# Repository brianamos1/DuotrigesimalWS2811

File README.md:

# DuotrigesimalWS2811
A board for driving 32 strings of pixels from a Teensy 4.1. Similar to the OctoWS2811, but with 32 outputs. 

This board interfaces with a Teensy 4.1, and is designed to use the OctoWS2811 library to drive up to 32 strings of LEDS. 

Version 0.2 is designed to use the Amphenol RJHSE508004-ND, which is a four port RJ45 jack.  Version 0.2a uses the Adam Tech MTJG-4-88GX1-FSB, which is a less expensive and more readily available alternative.

The 2x3 pin that connects the board to the Teensy 4.1's ethernet pins is available on digikey and mouser, however is easier to source from PJRC when purchasing the Teensy 4.1.  If you want the teensy to be removable, PJRC is the recommended source for that connector.  If you're going to solder the T4.1 to this board, then it doesn't matter the source for the pins.  ‎

Boards are available for purchase at https://www.tindie.com/products/25767/

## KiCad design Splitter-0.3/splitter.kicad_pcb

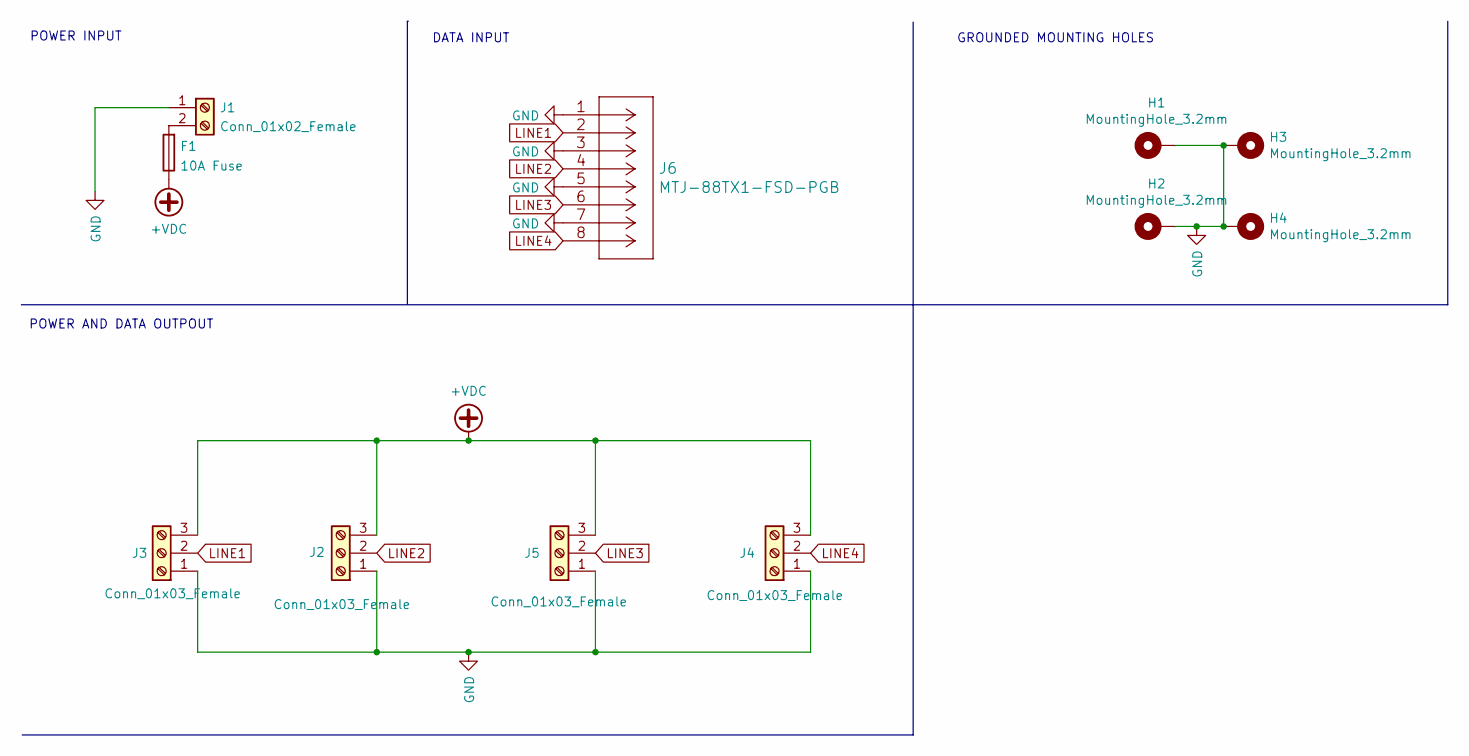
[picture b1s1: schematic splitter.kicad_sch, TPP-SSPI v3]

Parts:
F1: 10A Fuse; Fuseholder_Blade_Mini_Keystone_3568
H1, H2, H3, H4: MountingHole_3.2mm; MountingHole_3.2mm_M3_Pad_Via
J1: Conn_01x02_Female; TerminalBlock_OST_02A150-2_P2.54mm
J2, J3, J4, J5: Conn_01x03_Female; TerminalBlock_OST_03A150-3_P2.54mm
J6: MTJ-88TX1-FSD-PGB; RJ45_AdamTech_MTJ-88TX1-FSD-PGB

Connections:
+VDC: F1.1, J2.3, J3.3, J4.3, J5.3
GND: H1.1, H2.1, H3.1, H4.1, J1.1, J2.1, J3.1, J4.1, J5.1, J6.1, J6.3, J6.5, J6.7, J6.12, J6.13
LINE1: J3.2, J6.2
LINE2: J2.2, J6.4
LINE3: J5.2, J6.6
LINE4: J4.2, J6.8
unnamed: F1.2, J1.2

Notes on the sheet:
DATA INPUT
POWER INPUT
GROUNDED MOUNTING HOLES
POWER AND DATA OUTPOUT

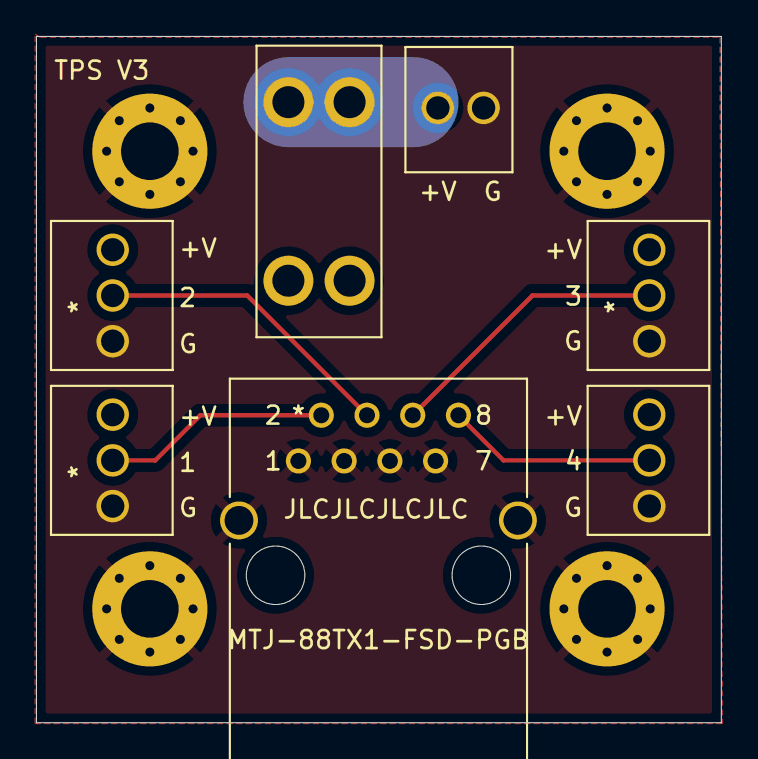
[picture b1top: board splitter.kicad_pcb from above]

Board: 2 copper layers, 38.0 x 38.1 mm, 11 parts (0 on the bottom side), 7 nets.

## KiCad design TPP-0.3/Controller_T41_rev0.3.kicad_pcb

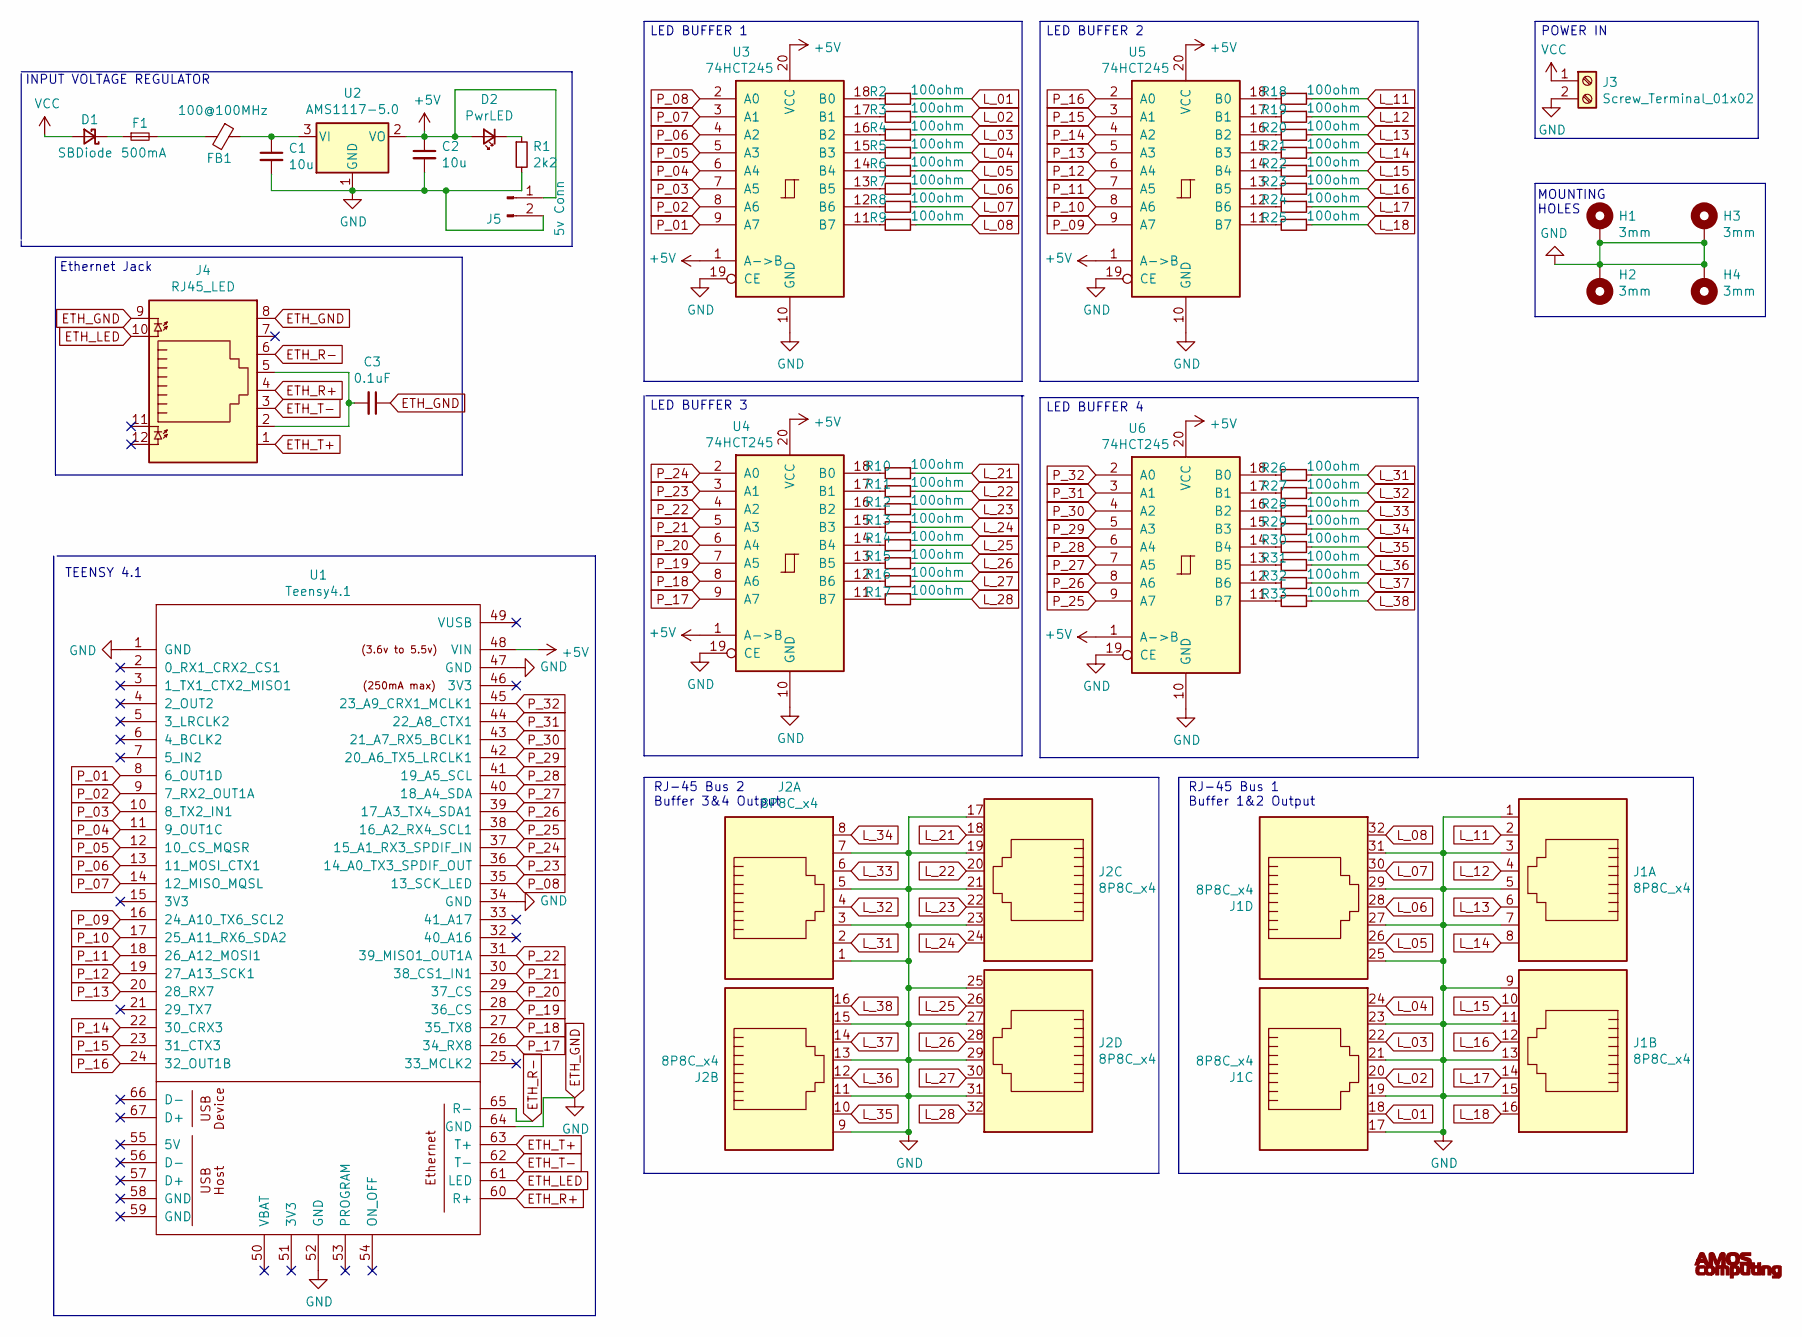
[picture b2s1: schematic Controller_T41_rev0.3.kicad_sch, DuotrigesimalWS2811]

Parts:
C1, C2: 10u; C_1206_3216Metric; LCSC C13585
C3: 0.1uF; C_0805_2012Metric; LCSC C49678
D1: SBDiode; D_SOD-123; Part Number B5819W; LCSC C8598
D2: PwrLED; LED_0603_1608Metric; LCSC C2286
F1: 500mA; Fuse_1206_3216Metric_Pad1.42x1.75mm_HandSolder
FB1: 100@100MHz; L_0805_2012Metric; Part Number GZ2012D101TF Ferrite Bead; LCSC C1015
H1, H2, H3, H4: 3mm; MountingHole_3.2mm_M3_Pad_Via
J1, J2: 8P8C_x4; RJ45_Amphenol_RJHSE508004-ND‎
J3: Screw_Terminal_01x02; TerminalBlock_Phoenix_MKDS-3-2-5.08_1x02_P5.08mm_Horizontal
J4: RJ45_LED; RJ45_Cetus_J1B1211CCD_Horizontal
J5: 5v Conn; PinHeader_1x02_P2.54mm_Vertical
R1: 2k2; R_0805_2012Metric; LCSC C17520
R2, R3, R4, R5, R6, R7, R8, R9, R10, R11, R12, R13, R14, R15, R16, R17, R18, R19, R20, R21, R22, R23, R24, R25, R26, R27, R28, R29, R30, R31, R32, R33: 100ohm; R_01005_0402Metric; LCSC C25076
U1: Teensy4.1; Teensy41
U2: AMS1117-5.0; SOT-223-3_TabPin2; LCSC C6187
U3, U4, U5, U6: 74HCT245; SOIC-20W_7.5x12.8mm_P1.27mm; LCSC C110789

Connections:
+5V: C2.1, D2.2 (A), J5.1, U1.48 (VIN), U2.2 (VO), U3.1 (A->B), U3.20 (VCC), U4.1 (A->B), U4.20 (VCC), U5.1 (A->B), U5.20 (VCC), U6.1 (A->B), U6.20 (VCC)
ETH_GND: C1.2, C2.2, C3.1, H1.1, H2.1, H3.1, H4.1, J1.1, J1.3, J1.5, J1.7, J1.9, J1.11, J1.13, J1.15, J1.17, J1.19, J1.21, J1.23, J1.25, J1.27, J1.29, J1.31, J2.1, J2.3, J2.5, J2.7, J2.9, J2.11, J2.13, J2.15, J2.17, J2.19, J2.21, J2.23, J2.25, J2.27, J2.29, J2.31, J3.2, J4.8, J4.9, J5.2, R1.2, U1.1 (GND), U1.34 (GND), U1.47 (GND), U1.52 (GND), U1.64 (GND), U2.1 (GND), U3.10 (GND), U3.19 (CE), U4.10 (GND), U4.19 (CE), U5.10 (GND), U5.19 (CE), U6.10 (GND), U6.19 (CE)
ETH_LED: J4.10, U1.61 (LED)
ETH_R+: J4.4, U1.60 (R+)
ETH_R-: J4.6, U1.65 (R-)
ETH_T+: J4.1, U1.63 (T+)
ETH_T-: J4.3, U1.62 (T-)
L_01: J1.18, R2.1
L_02: J1.20, R3.1
L_03: J1.22, R4.1
L_04: J1.24, R5.1
L_05: J1.26, R6.1
L_06: J1.28, R7.1
L_07: J1.30, R8.1
L_08: J1.32, R9.1
L_11: J1.2, R18.1
L_12: J1.4, R19.1
L_13: J1.6, R20.1
L_14: J1.8, R21.1
L_15: J1.10, R22.1
L_16: J1.12, R23.1
L_17: J1.14, R24.1
L_18: J1.16, R25.1
L_21: J2.18, R10.1
L_22: J2.20, R11.1
L_23: J2.22, R12.1
L_24: J2.24, R13.1
L_25: J2.26, R14.1
L_26: J2.28, R15.1
L_27: J2.30, R16.1
L_28: J2.32, R17.1
L_31: J2.2, R26.1
L_32: J2.4, R27.1
L_33: J2.6, R28.1
L_34: J2.8, R29.1
L_35: J2.10, R30.1
L_36: J2.12, R31.1
L_37: J2.14, R32.1
L_38: J2.16, R33.1
unnamed: C1.1, FB1.1, U2.3 (VI)
unnamed: C3.2, J4.2, J4.5
unnamed: D1.1 (K), F1.1
unnamed: D2.1 (K), R1.1
unnamed: F1.2, FB1.2
unnamed: R2.2, U3.18 (B0)
unnamed: R3.2, U3.17 (B1)
unnamed: R4.2, U3.16 (B2)
unnamed: R5.2, U3.15 (B3)
unnamed: R6.2, U3.14 (B4)
unnamed: R7.2, U3.13 (B5)
unnamed: R8.2, U3.12 (B6)
unnamed: R9.2, U3.11 (B7)
unnamed: R10.2, U4.18 (B0)
unnamed: R11.2, U4.17 (B1)
unnamed: R12.2, U4.16 (B2)
unnamed: R13.2, U4.15 (B3)
unnamed: R14.2, U4.14 (B4)
unnamed: R15.2, U4.13 (B5)
unnamed: R16.2, U4.12 (B6)
unnamed: R17.2, U4.11 (B7)
unnamed: R18.2, U5.18 (B0)
unnamed: R19.2, U5.17 (B1)
unnamed: R20.2, U5.16 (B2)
unnamed: R21.2, U5.15 (B3)
unnamed: R22.2, U5.14 (B4)
unnamed: R23.2, U5.13 (B5)
unnamed: R24.2, U5.12 (B6)
unnamed: R25.2, U5.11 (B7)
unnamed: R26.2, U6.18 (B0)
unnamed: R27.2, U6.17 (B1)
unnamed: R28.2, U6.16 (B2)
unnamed: R29.2, U6.15 (B3)
unnamed: R30.2, U6.14 (B4)
unnamed: R31.2, U6.13 (B5)
unnamed: R32.2, U6.12 (B6)
unnamed: R33.2, U6.11 (B7)
P_01: U1.8 (6_OUT1D), U3.9 (A7)
P_02: U1.9 (7_RX2_OUT1A), U3.8 (A6)
P_03: U1.10 (8_TX2_IN1), U3.7 (A5)
P_04: U1.11 (9_OUT1C), U3.6 (A4)
P_05: U1.12 (10_CS_MQSR), U3.5 (A3)
P_06: U1.13 (11_MOSI_CTX1), U3.4 (A2)
P_07: U1.14 (12_MISO_MQSL), U3.3 (A1)
P_08: U1.35 (13_SCK_LED), U3.2 (A0)
P_09: U1.16 (24_A10_TX6_SCL2), U5.9 (A7)
P_10: U1.17 (25_A11_RX6_SDA2), U5.8 (A6)
P_11: U1.18 (26_A12_MOSI1), U5.7 (A5)
P_12: U1.19 (27_A13_SCK1), U5.6 (A4)
P_13: U1.20 (28_RX7), U5.5 (A3)
P_14: U1.22 (30_CRX3), U5.4 (A2)
P_15: U1.23 (31_CTX3), U5.3 (A1)
P_16: U1.24 (32_OUT1B), U5.2 (A0)
P_17: U1.26 (34_RX8), U4.9 (A7)
P_18: U1.27 (35_TX8), U4.8 (A6)
P_19: U1.28 (36_CS), U4.7 (A5)
P_20: U1.29 (37_CS), U4.6 (A4)
P_21: U1.30 (38_CS1_IN1), U4.5 (A3)
P_22: U1.31 (39_MISO1_OUT1A), U4.4 (A2)
P_23: U1.36 (14_A0_TX3_SPDIF_OUT), U4.3 (A1)
P_24: U1.37 (15_A1_RX3_SPDIF_IN), U4.2 (A0)
P_25: U1.38 (16_A2_RX4_SCL1), U6.9 (A7)
P_26: U1.39 (17_A3_TX4_SDA1), U6.8 (A6)
P_27: U1.40 (18_A4_SDA), U6.7 (A5)
P_28: U1.41 (19_A5_SCL), U6.6 (A4)
P_29: U1.42 (20_A6_TX5_LRCLK1), U6.5 (A3)
P_30: U1.43 (21_A7_RX5_BCLK1), U6.4 (A2)
P_31: U1.44 (22_A8_CTX1), U6.3 (A1)
P_32: U1.45 (23_A9_CRX1_MCLK1), U6.2 (A0)
VCC: D1.2 (A), J3.1

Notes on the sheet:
INPUT VOLTAGE REGULATOR
MOUNTING HOLES
LED BUFFER 1
RJ-45 Bus 2 Buffer 3&4 Output
Ethernet Jack
LED BUFFER 4
POWER IN
LED BUFFER 2
RJ-45 Bus 1 Buffer 1&2 Output
LED BUFFER 3
TEENSY 4.1

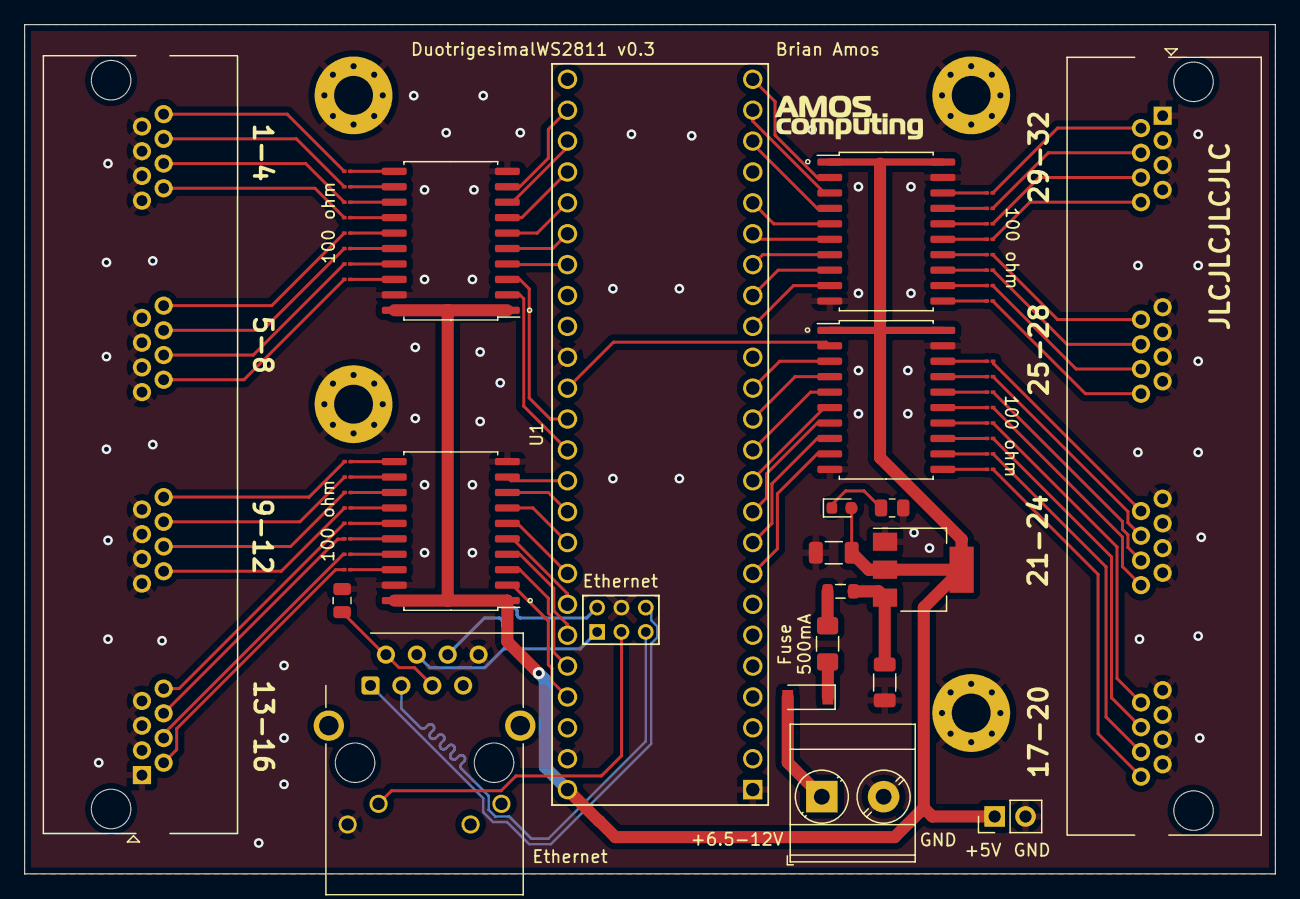
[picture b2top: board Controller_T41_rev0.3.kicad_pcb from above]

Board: 2 copper layers, 102.9 x 69.9 mm, 55 parts (0 on the bottom side), 109 nets.

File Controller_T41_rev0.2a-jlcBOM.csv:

Comment,Designator,Footprint,LCSC
"10u","C1,C2","Capacitor_SMD:C_1206_3216Metric","C13585"
"0.1uF","C3","Capacitor_SMD:C_0805_2012Metric","C49678"
"B5819W","D1","Diode_SMD:D_SOD-123","C8598"
"red","D2","LED_SMD:LED_0603_1608Metric","C2286"
"500mA","F1","Fuse:Fuse_0603_1608Metric_Pad1.05x0.95mm_HandSolder",""
"100@100MHz GZ2012D101TF","FB1","Inductor_SMD:L_0805_2012Metric"," C1015"
"3mm","H1,H2,H3,H4","MountingHole:MountingHole_3.2mm_M3_Pad_Via",""
"8P8C_x4","J1,J2","Controller_T41_rev0.2:MTJG-4-88GX1-FSB",""
"Screw_Terminal_01x02","J3","TerminalBlock_Phoenix:TerminalBlock_Phoenix_MKDS-3-2-5.08_1x02_P5.08mm_Horizontal",""
"RJ45_LED","J4","Connector_RJ:RJ45_Cetus_J1B1211CCD_Horizontal",""
"2k2","R1","Resistor_SMD:R_0805_2012Metric","C17520"
"100ohm","R2,R3,R4,R5,R6,R7,R8,R9,R10,R11,R12,R13,R14,R15,R16,R17,R18,R19,R20,R21,R22,R23,R24,R25,R26,R27,R28,R29,R30,R31,R32,R33","Resistor_SMD:R_1206_3216Metric","C17901"
"Teensy4.1","U1","teensy:Teensy41",""
"AMS1117-5.0","U2","Package_TO_SOT_SMD:SOT-223-3_TabPin2","C6187"
"74HCT245","U3,U4,U5,U6","Package_SO:SOIC-20W_7.5x12.8mm_P1.27mm","C110789"

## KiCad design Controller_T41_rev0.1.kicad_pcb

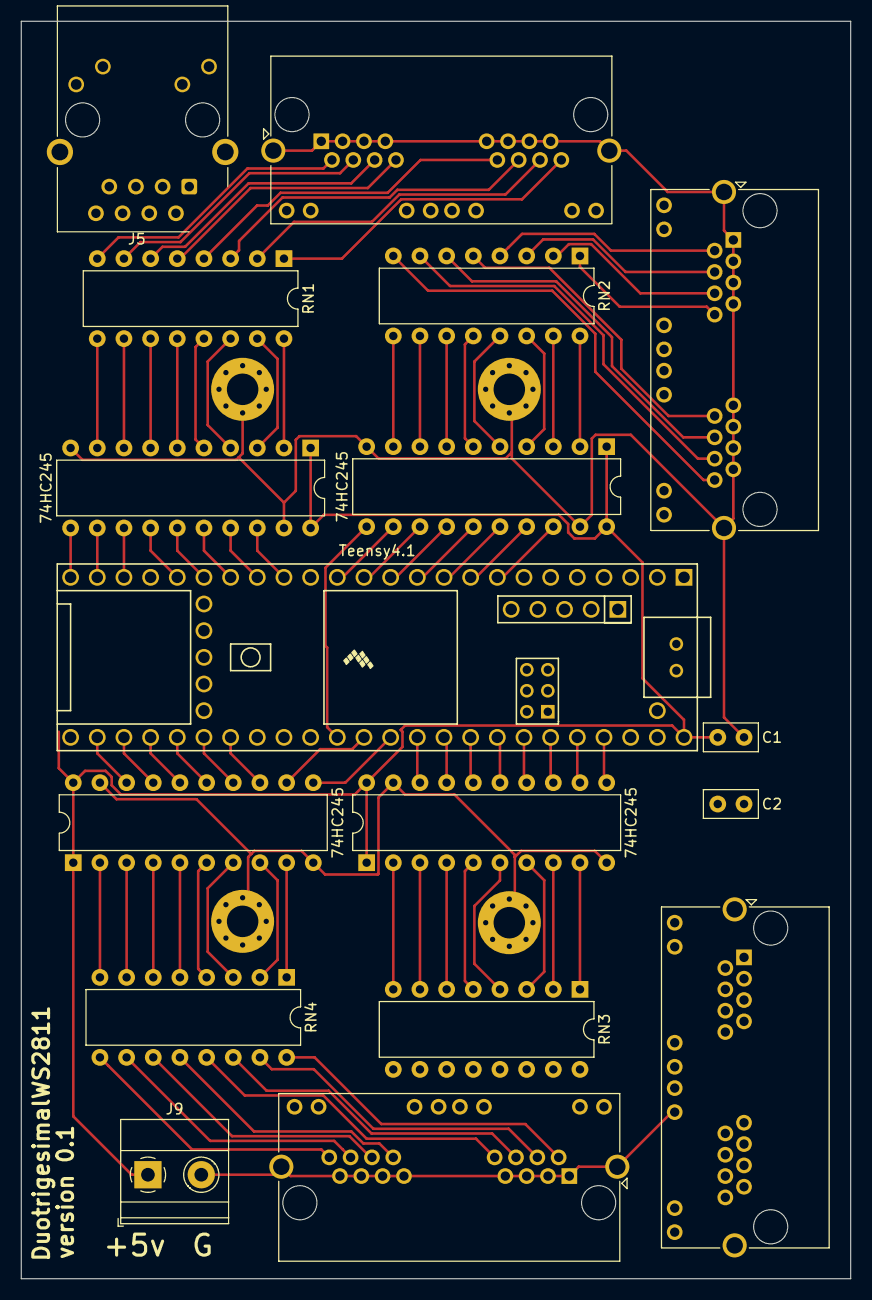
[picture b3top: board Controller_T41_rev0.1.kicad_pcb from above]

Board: 2 copper layers, 79.0 x 119.8 mm, 21 parts (0 on the bottom side), 105 nets.

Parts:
C1: 1uF; C_Disc_D5.0mm_W2.5mm_P2.50mm
C2: 0.1uF; C_Disc_D5.0mm_W2.5mm_P2.50mm
H1, H2, H3, H4: MountingHole_Pad; MountingHole_3mm_Pad_Via
J1, J2, J3, J4: RJ45_LED_Shielded_x2; RJ45_Amphenol_RJHSE538X-02
J5: RJ45_LED; RJ45_Cetus_J1B1211CCD_Horizontal
J9: Screw_Terminal_01x02; TerminalBlock_Phoenix_MKDS-1,5-2-5.08_1x02_P5.08mm_Horizont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
RN1, RN2, RN3, RN4: R_Pack08; DIP-16_W7.62mm
U1, U2, U4, U5: 74HC245; DIP-20_W7.62mm
U3: Teensy4.1; Teensy41

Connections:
GND: C1.1, H1.1, H2.1, H3.1, H4.1, J1.1, J1.3, J1.5, J1.7, J1.13, J1.15, J1.17, J1.19, J1.SH, J2.1, J2.3, J2.5, J2.7, J2.13, J2.15, J2.17, J2.19, J2.SH, J3.1, J3.3, J3.5, J3.7, J3.13, J3.15, J3.17, J3.19, J3.SH, J4.1, J4.3, J4.5, J4.7, J4.13, J4.15, J4.17, J4.19, J4.SH, J9.2, U1.10, U1.19, U2.10, U2.19, U3.47, U4.10, U4.19, U5.10, U5.19
unnamed: C1.2, J9.1, U1.1, U1.20, U2.1, U2.20, U3.48, U4.1, U4.20, U5.1, U5.20
unnamed: C2.1, J5.2, J5.5
unnamed: C2.2, J5.8, J5.9, U3.64
unnamed: J1.2, RN2.4
unnamed: J1.4, RN2.3
unnamed: J1.6, RN2.2
unnamed: J1.8, RN2.1
unnamed: J1.14, RN2.5
unnamed: J1.16, RN2.6
unnamed: J1.18, RN2.7
unnamed: J1.20, RN2.8
unnamed: J2.2, RN1.8
unnamed: J2.4, RN1.7
unnamed: J2.6, RN1.6
unnamed: J2.8, RN1.5
unnamed: J2.14, RN1.4
unnamed: J2.16, RN1.3
unnamed: J2.18, RN1.2
unnamed: J2.20, RN1.1
unnamed: J3.2, RN4.16
unnamed: J3.4, RN4.15
unnamed: J3.6, RN4.14
unnamed: J3.8, RN4.13
unnamed: J3.14, RN4.12
unnamed: J3.16, RN4.11
unnamed: J3.18, RN4.10
unnamed: J3.20, RN4.9
unnamed: J4.2, RN3.9
unnamed: J4.4, RN3.10
unnamed: J4.6, RN3.11
unnamed: J4.8, RN3.12
unnamed: J4.14, RN3.13
unnamed: J4.16, RN3.14
unnamed: J4.18, RN3.15
unnamed: J4.20, RN3.16
unnamed: J5.1, U3.63
unnamed: J5.3, U3.62
unnamed: J5.4, U3.60
unnamed: J5.6, U3.65
unnamed: J5.10, U3.61
unnamed: RN1.9, U1.9
unnamed: RN1.10, U1.8
unnamed: RN1.11, U1.7
unnamed: RN1.12, U1.6
unnamed: RN1.13, U1.5
unnamed: RN1.14, U1.4
unnamed: RN1.15, U1.3
unnamed: RN1.16, U1.2
unnamed: RN2.9, U2.9
unnamed: RN2.10, U2.8
unnamed: RN2.11, U2.7
unnamed: RN2.12, U2.6
unnamed: RN2.13, U2.5
unnamed: RN2.14, U2.4
unnamed: RN2.15, U2.3
unnamed: RN2.16, U2.2
unnamed: RN3.1, U4.9
unnamed: RN3.2, U4.8
unnamed: RN3.3, U4.7
unnamed: RN3.4, U4.6
unnamed: RN3.5, U4.5
unnamed: RN3.6, U4.4
unnamed: RN3.7, U4.3
unnamed: RN3.8, U4.2
unnamed: RN4.1, U5.9
unnamed: RN4.2, U5.8
unnamed: RN4.3, U5.7
unnamed: RN4.4, U5.6
unnamed: RN4.5, U5.5
unnamed: RN4.6, U5.4
unnamed: RN4.7, U5.3
unnamed: RN4.8, U5.2
unnamed: U1.11, U3.24
unnamed: U1.12, U3.23
unnamed: U1.13, U3.22
unnamed: U1.14, U3.20
unnamed: U1.15, U3.19
unnamed: U1.16, U3.18
unnamed: U1.17, U3.17
unnamed: U1.18, U3.16
unnamed: U2.11, U3.35
unnamed: U2.12, U3.14
unnamed: U2.13, U3.13
unnamed: U2.14, U3.12
unnamed: U2.15, U3.11
unnamed: U2.16, U3.10
unnamed: U2.17, U3.9
unnamed: U2.18, U3.8
unnamed: U3.26, U5.18
unnamed: U3.27, U5.17
unnamed: U3.28, U5.16
unnamed: U3.29, U5.15
unnamed: U3.30, U5.14
unnamed: U3.31, U5.13
unnamed: U3.36, U5.12
unnamed: U3.37, U5.11
unnamed: U3.38, U4.18
unnamed: U3.39, U4.17
unnamed: U3.40, U4.16
unnamed: U3.41, U4.15
unnamed: U3.42, U4.14
unnamed: U3.43, U4.13
unnamed: U3.44, U4.12
unnamed: U3.45, U4.11

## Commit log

2020-11-02 Initial Project
    Upload initial project
2020-11-02 Changes to be committed: modified: Controller_T41_rev0.1.kicad_pcb modified: Controller_T41_rev0.1.kicad_pcb-bak
2020-11-03 modified: Controller_T41_rev0.1.kicad_pcb modified: Controller_T41_rev0.1.kicad_pcb-bak modified: Controller_T41_rev0.1.net modified: Controller_T41_rev0.1.sch-bak modified: fp-info-cache
2020-11-06 updated board layout, converted rj-45 ports to dual rj-45 ports Converted design to kicad 5.
2020-11-07 modified: Controller_T41_rev0.1.kicad_pcb Added board outline.
2020-11-11 Switching to SMT components where possible
2020-11-16 Changes: bringing current version to 0.2, redrew schematic to make it more clear, using 2x4 port rj45 for output, new board layout with smt parts deleted: Controller_T41_rev0.1.kicad_pcb deleted: Con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
2020-11-16 Cleaning up files
2020-11-16 Minor changes to silkscreen
2020-11-18 Changed buffer to 74HCT245 from 74HC245
2020-11-21 Updated schematic layout and parts. Minor updates to footprint.
2020-11-21 new file: Controller_T41_rev0.2.pretty/logo.kicad_mod new file: Controller_T41_rev0.2.pretty/logo.lib
2020-11-21 deleted: Controller_T41_rev0.2.sch-bak
2020-12-30 new file: AC_Logo.kicad_mod
2020-12-30 added kicad generated board images
2020-12-30 Added render image
2020-12-30 Updated some parts on LCSC and some smt components
2021-01-01 Minor Updates
2021-01-01 Upgraded to Kicad 5.1.9
2021-01-01 Added headers to 3d view
2021-01-03 Minor Part Updates
2021-01-03 Initilized Version 0.3 with smaller components and better labeling.
2021-01-03 Smaller resistors, larger fuse, additional labeling on silkscreen
2021-01-04 Minor Placement Updates
2022-01-07 Adding a revision to 0.2 labeled 0.2a in order to use more available parts.
2022-01-08 added folder organization for different versions
2022-01-08 continue updating file locations
2022-01-08 Updated rev0.3 to KiCad 6
2022-01-08 added Splitter/Power Injector rev0.1
2022-01-16 Added version 3 of the splitter to this project

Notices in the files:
parts and their libraries:
Copyright 2021 Accelerated Designs. All rights reserved.
